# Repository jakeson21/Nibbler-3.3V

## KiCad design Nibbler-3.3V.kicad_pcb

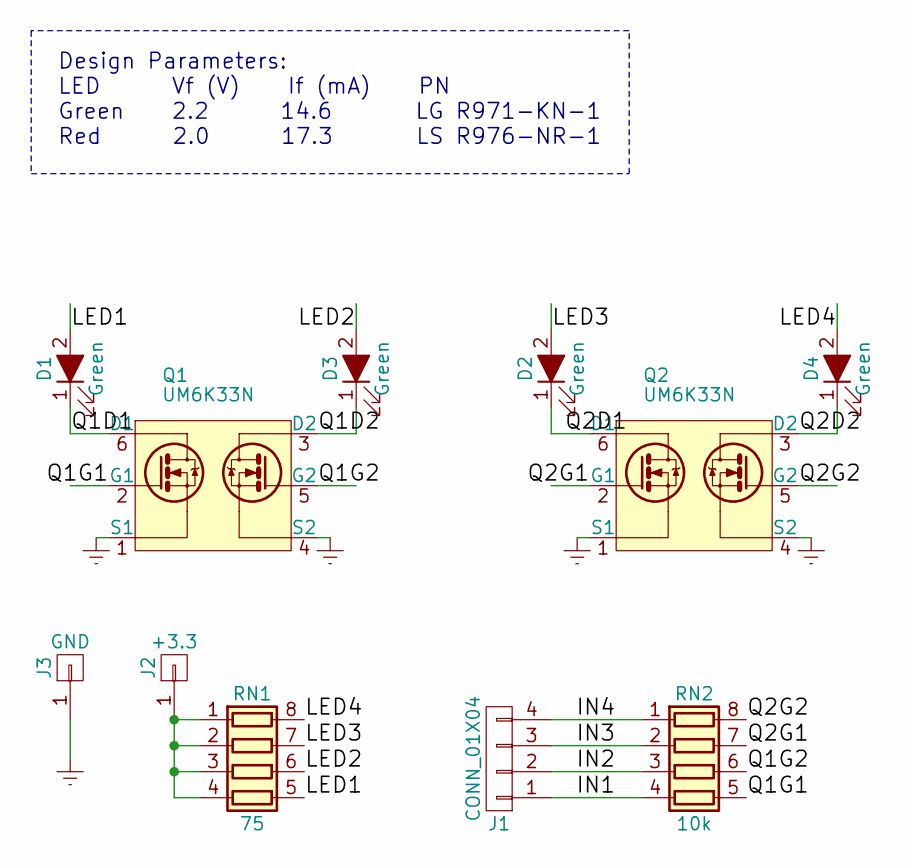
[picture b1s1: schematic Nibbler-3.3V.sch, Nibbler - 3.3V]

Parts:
D1, D2, D3, D4: Green; LED_0805_HandSoldering; Part Number LG R971-KN-1
J1: CONN_01X04; Pin_Header_Angled_1x04_Pitch2.54mm; Part Number PRPC004SBAN-M71RC
J2: +3.3; Pin_Header_Straight_1x01_Pitch2.54mm
J3: GND; Pin_Header_Straight_1x01_Pitch2.54mm
Q1, Q2: UM6K33N; SOT-363_SC-70-6; Part Number UM6K33NTN
RN1: 75; YC164-JR-0775RL; Part Number YC164-JR-0775RL
RN2: 10k; YC164-JR-0775RL; Part Number YC164-JR-0710KL

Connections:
/IN1: J1.1, RN2.4 (R4.1)
/IN2: J1.2, RN2.3 (R3.1)
/IN3: J1.3, RN2.2 (R2.1)
/IN4: J1.4, RN2.1 (R1.1)
/LED1: D1.2 (A), RN1.5 (R4.2)
/LED2: D3.2 (A), RN1.6 (R3.2)
/LED3: D2.2 (A), RN1.7 (R2.2)
/LED4: D4.2 (A), RN1.8 (R1.2)
/Q1D1: D1.1 (K), Q1.6 (D1)
/Q1D2: D3.1 (K), Q1.3 (D2)
/Q1G1: Q1.2 (G1), RN2.5 (R4.2)
/Q1G2: Q1.5 (G2), RN2.6 (R3.2)
/Q2D1: D2.1 (K), Q2.6 (D1)
/Q2D2: D4.1 (K), Q2.3 (D2)
/Q2G1: Q2.2 (G1), RN2.7 (R2.2)
/Q2G2: Q2.5 (G2), RN2.8 (R1.2)
GNDREF: J3.1, Q1.1 (S1), Q1.4 (S2), Q2.1 (S1), Q2.4 (S2)
unnamed: J2.1, RN1.1 (R1.1), RN1.2 (R2.1), RN1.3 (R3.1), RN1.4 (R4.1)

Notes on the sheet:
Design Parameters: LED Vf (V) If (mA) PN Green 2.2 14.6 LG R971-KN-1 Red 2.0 17.3 LS R976-NR-1

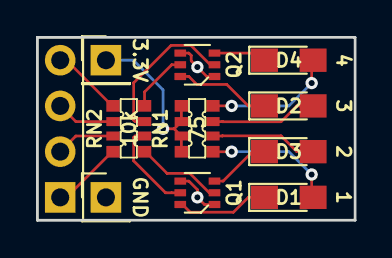
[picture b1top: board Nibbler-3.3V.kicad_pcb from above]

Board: 2 copper layers, 17.7 x 10.2 mm, 11 parts (0 on the bottom side), 18 nets.

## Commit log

2017-07-30 Version submitted to OSH Park (v0.1)
2017-07-30 Renaming project to Nibbler-3.3V since this board is not truly specific to green LEDs as originally intended.
2017-09-16 Minor layout rework - rotated current limit resistor in layout and reversed LED connections in schematic. Modified bottom silkscreen text
